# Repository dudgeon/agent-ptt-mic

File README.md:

# Claude Code Companion Peripheral

A single USB-C peripheral, built on a Seeed Studio XIAO RP2040, that
enumerates — with no driver install — as both a USB HID keyboard and a USB
Audio Class microphone at the same time. Physical controls handle push-to-talk
microphone activation, an always-on latch, and the keystrokes Claude Code uses
for its permission/approval prompts.

## Status

Pre-hardware-arrival, breadboard-planning phase. The RP2040 board has been
ordered but hasn't shipped yet. See [`docs/STATUS.md`](docs/STATUS.md) for the
live progress tracker.

## Start here

- [`docs/SPEC.md`](docs/SPEC.md) — the full project specification: verbatim
  requirements from the project owner, locked decisions, open questions, pin
  map, and the milestone-by-milestone work plan. This is the single source of
  truth; there is no other record of these requirements.
- [`docs/STATUS.md`](docs/STATUS.md) — current progress against the milestone
  plan and open questions.
- [`CLAUDE.md`](CLAUDE.md) — quick orientation for a coding agent picking this
  project up.

## Repo layout

```
docs/       spec + status
firmware/   RP2040 firmware (Pico SDK + TinyUSB)
hardware/   BOM, wiring notes, breadboard/PCB assets
```

## Hardware

- **MCU:** Seeed Studio XIAO RP2040 ([product page](https://www.seeedstudio.com/XIAO-RP2040-v1-0-p-5026.html), [wiki](https://wiki.seeedstudio.com/XIAO-RP2040/))
- **Mic:** I2S MEMS breakout (SPH0645 recommended, not yet purchased)
- **Controls:** 5 momentary buttons + 1 latching switch (see `docs/SPEC.md` §8 for the pin map)

## Work plan

See `docs/SPEC.md` §12 for the full milestone breakdown (M1–M7). In short:
toolchain bring-up → HID-only → UAC2-only (synthetic tone) → composite
HID+UAC2 device (highest-risk step) → real mic → buttons/gating/LED →
freeze for custom PCB handoff.

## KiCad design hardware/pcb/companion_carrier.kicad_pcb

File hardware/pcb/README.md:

# Carrier PCB — KiCad project

2-layer carrier board (44 × 104 mm) for the handheld device: hosts the XIAO
RP2040 module (**pre-soldered/header SKU**, mounted on the BACK via its own
header pins, USB-C facing away into the back shell), 5× Kailh Choc V1
keyswitches, the **C&K OS102011MA1QN1** side-actuated latch slide (THT,
right-angle — replaced the obsolete PCM12SMTR, issue #16), an I2S mic
**breakout module** (front side, THT header), an **addressable RGB LED**
(WS2812B/SK6812-style — the one deliberately-reintroduced SMD part, see
below) + THT passives — every other active part is through-hole/header-
mount, hand-solderable with a plain iron (2026-07-02 revision; see
`docs/PHYSICAL_DESIGN_SPEC.md` §7 for why). Net/pin assignments follow
`docs/SPEC.md` §8 plus the status LED on spare D10/GPIO3 — the full
netlist table is in `../BOM.md`. Front silkscreen carries
`agent-ptt-mic-v0 / Geoff Dudgeon & Claude` (Geoff's request, 2026-07-02).

**Why the LED is SMD again:** Geoff asked for a true RGB status LED. A
discrete (non-addressable) RGB LED needs 3 independent GPIOs; the locked
pin map only has 2 spares. An addressable LED needs just 1 data pin, so
it's the only option that fits — still hand-solderable (large gull-wing
pads), just not through-hole.

## Files

- `generate_pcb.py` — the source of truth for placement + netlist.
  Regenerates the board file from `../design_params.py`. Run
  `python3 hardware/pcb/generate_pcb.py` from the repo root after changing
  any dimension or position — **then re-run the routing pipeline below**
  (regenerating discards routing).
- `route_board.py` — step 2: headless routing via freerouting + zone fill.
  Needs KiCad's bundled python (for `pcbnew`) and a freerouting jar; see
  its docstring for exact invocation.
- `companion_carrier.kicad_pcb` — generated, **routed** output (committed).
- `companion_carrier.kicad_pro` — project file.
- `fab/companion_carrier_v0_gerbers.zip` — Gerbers + Excellon drill files,
  ready for JLCPCB/PCBWay upload.
- `fab/companion_carrier-cpl.csv` — component placement (pos) file for
  PCBA quoting.
- `fab/board_top.png`, `fab/board_bottom.png` — 3D renders of the routed
  board (`kicad-cli pcb render`).

## Status: ROUTED, DRC-clean (2026-07-02)

Routed headlessly with KiCad 10.0.4 + freerouting 2.2.4 (the repo's old
"route interactively" rule was about having real DRC, not about hands on
a mouse — this pipeline runs KiCad's own DRC):

```
python3 hardware/pcb/generate_pcb.py
<kicad-python> hardware/pcb/route_board.py <freerouting.jar>
kicad-cli pcb drc --severity-error --exit-code-violations ...
kicad-cli pcb export gerbers/drill/pos ...
```

Final DRC: **0 error-severity violations, 0 unconnected items.** Remaining
warnings are cosmetic (silk-over-copper clips at fab, generated footprints
aren't from a library, two unmirrored back-silk ref texts). Two real
issues were caught and fixed by the first DRC run: R1's +X pad landed on
SW6's pin 1 (R1 moved to x=8), and SW6's support-leg pads sat 0.25mm from
the board edge (moved to the footprint centreline). SW5's GND pad uses a
solid zone connection instead of thermal spokes — the PTT switch's
stem/post holes crowd the F.Cu zone below the 2-spoke DRC minimum.

There is intentionally no `.kicad_sch`: the circuit is 17 components with a
one-net-per-switch topology, fully specified by the netlist table in
`../BOM.md` and encoded on the pads here. Drawing a schematic in KiCad from
that table is mechanical; hand-writing `.kicad_sch` s-expressions without
KiCad available to validate them is where errors would creep in.

## Before ordering fabrication — VERIFY list

Gerbers exist and DRC is clean, but footprint geometry is still
datasheet-derived. Before actually placing a fab order, check against
physical parts:

1. **XIAO header pin holes** — drill/pad size (currently 1.0mm drill,
   1.8mm pad) must fit the actual presoldered pin diameter; check against
   the physical board, not just a generic 0.1" header assumption.
2. **XIAO pin order** — the module is placed USB-down, back side; the
   pad-to-net map in `generate_pcb.py` encodes the 180° rotation of
   Seeed's USB-up pinout drawing. Sanity-check against a physical board
   before soldering.
3. **XIAO standoff/pin length** — `design_params.py XIAO_MODULE_STANDOFF`
   (6.0mm) is an estimate for how far the module hangs off the carrier;
   measure the real pin length before finalizing the enclosure thickness.
4. **SW6 land pattern (`slide_os102()`)** — C&K OS102011MA1QN1, pin/
   support-hole pattern from the OS series datasheet (3× ø0.8 @ 2.1mm +
   2× ø1.5 @ 8.2mm span). The pin row's exact X offset within the body
   and the support-leg offset were read off the drawing at print
   precision — measure a physical part before ordering.
5. **Mic breakout footprint** — `MIC_BRK_L`/`MIC_BRK_W`/`MIC_BRK_H`
   **confirmed 2026-07-02** against Adafruit's own listing for #3421
   (16.7 × 12.7 × 1.8mm) — no longer an estimate, `design_params.py`
   updated. Pin pitch (2.54mm, 6-pin header) still assumed standard —
   worth a quick physical check but low risk.
6. **Choc contact-pin handedness** — pin 2 at (5.0, −3.8) assumes the common
   variant; check against a physical switch.
7. Re-run the route pipeline + DRC after any of the above change a
   dimension (regeneration discards routing — `route_board.py` re-routes
   in seconds).

## Coordinate convention

Board space: X = 0 at the board centreline, Y = 0 at the top (mic) edge,
+Y toward the USB-C end. Sheet offset (60, 30) mm. All positions come from
`../design_params.py` — edit there, not here.

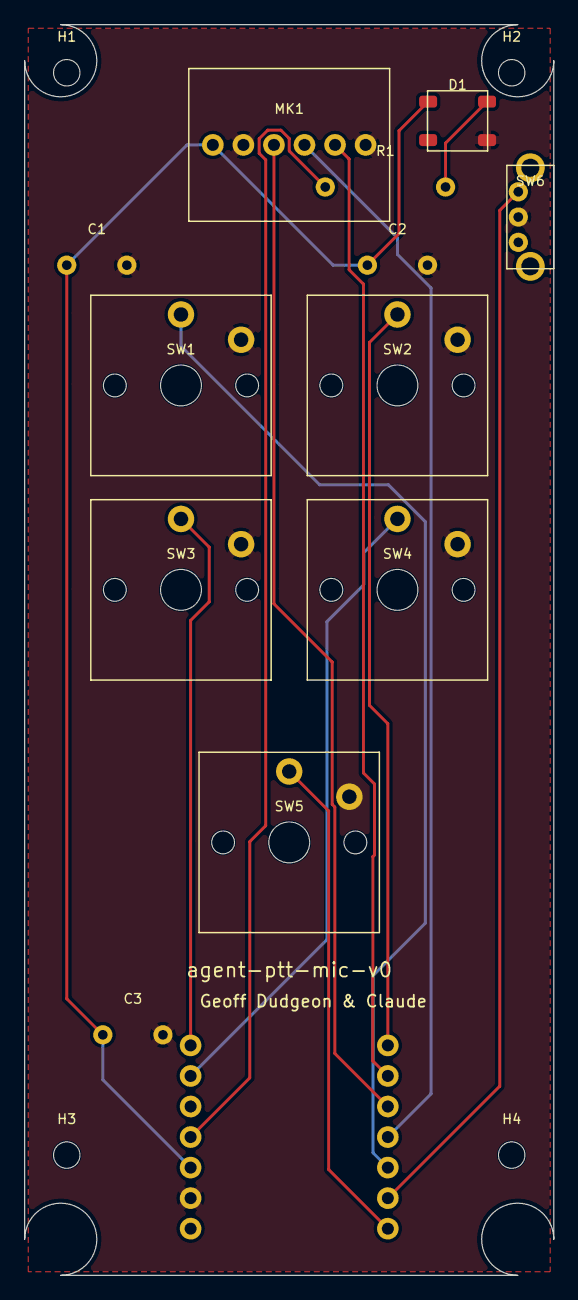
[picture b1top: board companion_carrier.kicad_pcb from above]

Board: 2 copper layers, 44.0 x 104.0 mm, 17 parts (1 on the bottom side), 13 nets.

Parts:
C1, C2, C3: THT_passive
D1: WS2812B_5050
H1, H2, H3, H4: MountingHole_M2
MK1: MicBreakout_SPH0645-style
R1: THT_passive
SW1, SW2, SW3, SW4, SW5: Kailh_Choc_V1
SW6: CK_OS102011MA1QN1
U1: XIAO-RP2040_preSoldered_header

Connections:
3V3: C1.1, C2.1, C3.1, D1.1, MK1.P1, U1.L5
GND: C1.2, C2.2, C3.2, D1.3, MK1.P2, MK1.P6, SW1.2, SW2.2, SW3.2, SW4.2, SW5.2, SW6.2, U1.L6
I2S_BCLK: MK1.P3, U1.R3
I2S_LRCLK: MK1.P5, U1.R2
I2S_SD: MK1.P4, U1.R4
KEY_APPROVE: SW1.1, U1.R5
KEY_MODE: SW4.1, U1.L2
KEY_REJECT: SW3.1, U1.L1
KEY_REMEMBER: SW2.1, U1.R1
LATCH: SW6.1, U1.R6
LED_DATA: R1.1, U1.L4
LED_DIN: D1.4, R1.2
PTT: SW5.1, U1.R7

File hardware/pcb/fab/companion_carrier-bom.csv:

Comment,Designator,Footprint,JLCPCB Part #（optional）
Seeed Studio XIAO RP2040 Pre-Soldered,U1,XIAO_RP2040_Header,
Kailh Choc V1 (PG1350) keyswitch,"SW1,SW2,SW3,SW4,SW5",Kailh_Choc_V1,
C&K OS102011MA1QN1 slide switch,SW6,CK_OS102011MA1QN1,C226259
I2S MEMS mic breakout (Adafruit SPH0645-style),MK1,MicBreakout_SPH0645-style,
WS2812B/SK6812 addressable RGB LED (5050),D1,LED_5050_Addressable,
100nF ceramic capacitor THT,"C1,C2",CAP-THT_5mm,
10uF electrolytic/ceramic capacitor THT,C3,CAP-THT_5mm,
300-500ohm 1/4W axial resistor,R1,RES-THT_10mm,
